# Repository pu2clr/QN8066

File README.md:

# [QN8066 FM DSP RX/TX  Arduino Library](https://pu2clr.github.io/QN8066/)

This library is intended to provide an easy-to-use interface for controlling the QN8066 FM transceiver and receiver. 

The primary goal of this Arduino library project for the QN8066 is to simplify the development of robust applications using this device. I hope that hobbyists, electronics technicians, radio amateurs, and others interested in this work will find success in their projects. All the C/C++ functions and methods are documented [here](https://pu2clr.github.io/QN8066/extras/apidoc/html/index.html).

This library can be freely distributed using the [MIT Free Software model](https://github.com/pu2clr/QN8066/blob/main/LICENSE). 
By using or installing this library, you are agreeing to the terms of the [MIT license](https://github.com/pu2clr/QN8066/blob/main/LICENSE). 

[Copyright (c) 2024 Ricardo Lima Caratti](https://github.com/pu2clr/QN8066/blob/main/LICENSE). 

Contact: __pu2clr@gmail.com__.

## About Me

I hold a Master's degree in Educational Technology from the Federal University of Ceará, where I delved into the ways technology can enhance learning experiences. My passion for computer science led me to specialize in it, focusing on Distributed Systems Development with an Object-Oriented approach, at the University of Brasília. My academic journey began with a Bachelor's degree in Information Systems from the União Pioneira de Integração Social (UPIS-Brasília). Outside the classroom, my main hobbies are electronics and Amateur Radio. 

## Notice to Users Regarding this Library

*This library is continuously evolving, with both corrective and feature updates. While the implemented functions have been tested, it is possible that in certain situations, the library may exhibit unexpected behavior. I encourage users to always utilize the latest release of this library. Should you encounter any issues, please feel free to contact me at pu2clr@gmail.com. I will do my best to address or clarify any problems as quickly as possible. Thank you.*

## Contents

1. [Legal Compliance Guidelines](./#legal-compliance-guidelines)
2. [QN8066 Arduino Library Features](./#qn8066-arduino-library-features)
2. [Technical Overview of the QN8066 RX/TX Device (IC)](./#technical-overview-of-the-qn8066-rxtx-device-ic)
3. [Why a QN8066 library for Arduino?](./#why-a-qn8066-library-for-arduino)
4. [Groups and Forums](./#groups-and-forums)
5. [QN8066 Functional Blocks](./#qn8066-functional-blocks)
6. [QN8066 PINOUT](./#qn8066-pinout)
7. [QN8066 Summary of User Control Registers](./#qn8066-summary-of-user-control-registers)
8. [QN8066 and Arduino based on ATmega328 or LGT8F328](./#qn8066-and-arduino-based-on-atmega328-or-lgt8f328)
9. [Homemade setup with the QN8066](./#homemade-setup-with-the-qn8066)
10. [DIY Kit 5W-7W FM Transceiver](./#diy-kit-5w-7w-fm-transceiver)
11. [Arduino Library Documentation](https://pu2clr.github.io/QN8066/extras/apidoc/html/index.html)
12. [**Arduino Sketch examples**](https://github.com/pu2clr/QN8066/tree/main/examples)
13. [Examples Index](./#examples-index)
14. [Boards where this library can be compiled](./#boards-where-this-library-can-be-compiled)
15. [Donate](./#donate)
16. [Most Frequent Problems](./#most-frequent-problems)
17. [References](./#references)

## Legal Compliance Guidelines

### Important Notice

It is important to emphasize that the project presented here is not intended to encourage anyone to violate their country’s regulations regarding radio frequency emissions. The goal of this project, centered around an Arduino library for controlling the QN8066, is to facilitate the development of diverse solutions involving this device.

Please, be aware that the use of FM transmitters is regulated by the laws and regulations of each country. **It is crucial to ensure that your use of any FM transmitter complies with the applicable legal requirements and does not violate any broadcasting regulations**.

### Legal Compliance Guidelines

1. **Frequency Range**: Ensure that the frequency range used by your FM transmitter is permitted in your country.
2. **Transmission Power**: Adhere to the maximum allowed transmission power to avoid interference with licensed broadcasters and other communication services.
3. **Licensing**: Check if a license is required to operate an FM transmitter in your region. Obtain the necessary permissions if required.
4. **Interference**: Avoid causing interference with other electronic devices and communication services. Ensure your setup follows the prescribed technical standards.
5. **Public Safety**: Be mindful of public safety and ensure your use of the FM transmitter does not pose any risks.

By following these guidelines, you can ensure that your use of the FM transmitter respects the laws and regulations of your country and does not result in any legal issues.

### Brazilian legislation notes

* Brazilian legislation allows some flexibility for the use of frequencies for research, experimentation, and educational purposes.
* FM transmitters with very low power (up to 0.5 mW) and short range can operate without a license. 
* Although amateur radio does not cover the commercial FM band, it is regulated by Anatel and permits transmission experimentation on other frequencies to promote technical learning.
* For educational or field transmissions, special authorization can be requested for specific events, such as science fairs or public demonstrations.
* Experimental transmissions may be allowed in controlled environments, such as laboratories, provided the signal does not exceed the physical boundaries of the location or interfere with other services.
* Microtransmitters or prototypes for short-range testing are tolerated as long as they operate within specific bands or with extremely low power.
* Wireless microphones based on FM transmitters are legal if they comply with designated sub-bands and power limits to prevent interference. 
* Community radio stations, limited to 25 watts and a 4 km radius, require licenses granted to non-profit organizations through the Ministry of Communications, with permits valid for 10 years and restrictions on commercial advertising.

# Groups and Forums

There is a Facebook group called [QN80XX FM Transmitters & Receivers Enthusiasts](https://www.facebook.com/groups/qn80xx)  where the purpose is exchanging experiences with projects based on Quintic QN80XX IC family. You will be welcome there.

## Donate 

If you find this project useful, consider making a donation so that the author of this library can purchase components and modules for improvements and testing of this library. [Click here to donate](https://www.paypal.com/donate/?business=LLV4PHKTXC4JW&no_recurring=0&item_name=Consider+making+a+donation.+So%2C+I+can+purchase+components+and+modules+for+improvements+and+testing+of+this+library.&currency_code=USD) or use the QR code below.

## Acknowledgements

* __Mr. Grazianny Carvalho Tavares__ - I would like to thank Mr. Grazianny Carvalho Tavares, PU7MGR, for introducing me to the QN8066 and encouraging me to develop this library. Mr. Grazianny also played a crucial role in helping me understand various concepts about FM modulation, audio quality criteria, as well as in testing the fundamental functions implemented in this library using equipment for precise value measurements.

* I would like to thank Mr. __Adam Fabio__ for his article published in the online magazine [Hackaday](https://hackaday.com) titled *[Be Your Own DJ With QN8066 And An Arduino Library](https://hackaday.com/2024/08/10/be-your-own-dj-with-qn8066-and-an-arduino-library/)*.

* I would like to thank Mr. __Gareth Halfacree__ for his article published in the online magazine  [hackster.io](https://www.hackster.io) titled *[Ricardo Lima Caratti's Handy Arduino Library Delivers Easy QN8066-Powered FM Radio Projects](https://www.hackster.io/news/ricardo-lima-caratti-s-handy-arduino-library-delivers-easy-qn8066-powered-fm-radio-projects-474213406313)*.

* Mr. Elionaldo Gomes da Silva, PY2EGS, to share his [board Layout project with Nano and LCD](./extras/schematics/NANO_LCD16x2_BOARD/)

## Why a QN8066 library for Arduino?

Technically, no Arduino application strictly requires a library. In some cases, avoiding libraries might even be the right decision. However, there are several compelling reasons to consider using them.

Libraries often simplify the design and maintenance of code, and they can make your projects more portable by implementing the necessary functionality across multiple hardware platforms.

For example, if you want to use an LCD or another display device in a project that monitors temperature and atmospheric pressure, there are many excellent libraries available for Arduino users. These libraries usually include most, if not all, of the features you might need. Re-inventing the wheel by not using a library generally doesn't make sense—unless you need a feature that no existing library supports. Using a library is often the smarter choice, particularly when it can simplify porting your code to different hardware.

Utilizing a library can reduce programming complexity and enhance the robustness of your application. It simplifies life not only for other developers but also for yourself. You don't need to be a software engineer to see the value in this. A library is similar to an integrated circuit (IC); while you could manually implement the functionality of many ICs in a circuit, doing so would significantly increase the cost, complexity, size, and potential for failure of your project. Often, it's better to abstract certain functions inside a ready-made IC. The user only needs to know how to interact with the chip, not how the chip itself is designed.

Finally, if you're already using libraries to handle the I2C bus (Wire.h), TFT or OLED displays, SPI devices, and Serial UART communication, it makes sense to use a library to manage the QN8066 device as well. The QN8066 Arduino Library can add convenience, development speed, and robustness to your project. Unlike closed-source solutions, this library is open-source, allowing you to learn from and modify the code as needed.

### Efficient Use of Libraries in Microcontroller Applications

Among the common myths about using this library alongside others is the assumption that it could significantly increase the final code size, making the application unfeasible for many microcontrollers. However, it is essential to highlight that, although the library contains extensive code, a large portion serves to provide directives to the C/C++ compiler and does not necessarily translate into executable code. Examples include type definitions (typedef), data structures (struct), and unions (union). Additionally, modern compilers and linkers offer powerful optimization features, notably [Link Time Optimization (LTO)](https://gcc.gnu.org/projects/lto/lto.pdf), which eliminates unused symbols and code, ensuring the final binary is lean and efficient. These optimizations, combined with dead code elimination and [inlining strategies](https://ethz.ch/content/dam/ethz/special-interest/infk/ast-dam/documents/Theodoridis-ASPLOS22-Inlining-Paper.pdf), reduce the overhead, making the use of complex libraries feasible even in resource-constrained environments.

In light of this, to make the most of your application, it is essential to have a deep understanding of the microcontroller architecture you are working with, as well as the tools you are using, such as the compiler and linker.

#### See also: 

 * [Inline Functions](https://isocpp.org/wiki/faq/inline-functions)
 * [Understanding and Exploiting Optimal Function Inlining](https://ethz.ch/content/dam/ethz/special-interest/infk/ast-dam/documents/Theodoridis-ASPLOS22-Inlining-Paper.pdf)
 * [Inline C++ code in embedded applications](https://blogs.sw.siemens.com/embedded-software/2020/07/20/inline-c-code-in-embedded-applications/)
 * [LLVM Link Time Optimization: Design and Implementation](https://llvm.org/docs/LinkTimeOptimization.html#llvm-link-time-optimization-design-and-implementation)
 * [What is Link Time Optimization (LTO)](https://developer.arm.com/documentation/101458/2404/Optimize/Link-Time-Optimization--LTO-/What-is-Link-Time-Optimization--LTO-)
 * [Link-Time Optimization in GCC: Requirements and High-Level Design](https://gcc.gnu.org/projects/lto/lto.pdf)
 * [How to use the typedef struct in C](https://www.educative.io/answers/how-to-use-the-typedef-struct-in-c)
 * [Structures, Typedef and Union in C Programming](https://binaryupdates.com/structures-typedef-union-in-c-programming/)
 * [Bit Fields in C](https://www.geeksforgeeks.org/bit-fields-c/)

## QN8066 Arduino Library Features

This library uses the I²C communication protocol and implements most of the functions offered by QN8066 IC from QUINTIC. This library also has primitive functions that make it easier for you to implement commands that may not have been implemented yet. As said before, this library is constantly improving. Check the API documentation before implementing a new function. It is likely that your function is already implemented. [See the API documentation for this library](https://pu2clr.github.io/QN8066/extras/apidoc/html/index.html). 

1. **Open Source**. It is free. You can use, copy, modify, merge, publish, distribute, sublicense, and/or sell copies of the Software. See [MIT License](https://github.com/pu2clr/QN8066/blob/main/LICENSE) to know more.   
2. Built based on QN8066 Datasheet
3. C++ Language and Object-oriented programming. You can easily extend the QN8066 class by adding more functionalities. 
4. **API Documentation**. All functions implemented in this library have documentation that can be checked in the source code or at this [link](https://pu2clr.github.io/QN8066/extras/apidoc/html/index.html)
4. Available on Arduino IDE (via Manage Libraries). Easy to install and use. 
5. **Cross-platform**. You can compile and run this library on most of boards supported by the Arduino IDE (Examples: ATtiny85, boards based on ATmega328 and ATmega-32u4, ATmega2560, ARM Cortex, STM32, Arduino DUE, ESP32 and more). 
6. Simplifies projects based on QN8066
7. [A lot of examples to guide the user](https://github.com/pu2clr/QN8066/tree/master/examples)
8. RDS support
9. **Clock reference selection** - The QN8066 has a pin (XCLC) that should be used to inject a signal that will be utilized by the IC as a reference clock. This signal can be 32.768 kHz or a multiple of this value. This library allows you to adapt your project to the active crystal you have available. See below for more details about it. 

## Technical Overview of the QN8066 RX/TX Device (IC)

### Introduction

The QN8066 is a highly integrated and versatile receiver/transmitter (RX/TX) device designed for use in FM radio applications. It offers a comprehensive solution for high-quality audio reception and transmission with minimal external components, making it suitable for a wide range of applications, including portable radios, automotive systems, and multimedia devices.

#### Key Features

- **Frequency Range**: The QN8066 operates over a wide frequency range, supporting FM band frequencies from 64 MHz to 108 MHz.
- **High Sensitivity**: The device is engineered to provide excellent sensitivity, allowing for clear reception of weak signals.
- **Integrated Analog and Digital Functions**: It includes both analog and digital components, ensuring compatibility with various audio formats and enhancing overall functionality.
- **Stereo Decoder**: The integrated stereo decoder ensures high-fidelity stereo audio output.
- **Low Power Consumption**: Designed with power efficiency in mind, the QN8066 is suitable for battery-powered devices, extending operational life.
- **Digital Signal Processing (DSP)**: Advanced DSP capabilities improve signal quality and reduce noise and interference.
- **Programmable Interface**: The QN8066 offers a flexible, programmable interface, enabling easy integration and customization for specific applications.

#### Technical Specifications

- **Operating Voltage**: The device operates at a typical voltage range of 2.7V to 3.6V.
- **Current Consumption**: It features low current consumption, typically around 20mA during active operation.
- **Output Power**: The output power is adjustable, catering to different transmission requirements.
- **Modulation Modes**: Supports various modulation modes including mono, stereo, and digital audio formats.
- **Interface**: I2C interface for easy communication with microcontrollers and other digital systems.

#### Applications

- **Portable Radios**: Due to its compact size and low power consumption, the QN8066 is ideal for portable radio applications.
- **Automotive Systems**: The high sensitivity and DSP capabilities make it suitable for in-car entertainment systems.
- **Multimedia Devices**: Compatible with a variety of audio sources, the QN8066 can be integrated into multimedia devices requiring FM reception and transmission capabilities.

## QN8066 Functional Blocks

1. **RF Front-End**: The RF front-end is designed to efficiently capture and process FM signals, ensuring minimal loss and high-quality signal reception.
2. **PLL Synthesizer**: The phase-locked loop (PLL) synthesizer ensures stable frequency generation and accurate tuning.
3. **Audio Processing**: Includes both analog and digital audio processing units to enhance sound quality and support various audio formats.
4. **Power Management**: Advanced power management features optimize power consumption, making the QN8066 ideal for portable applications.

### Attention

* __The Logic signals level of the QN8066 device (CEN, SCL, SDA, to GND) works from 1.6V to 3.6V (see Datasheet, ELECTRICAL SPECIFICATIONS, section Recommended Operating Conditions). If you are using a 5V Arduino board, that Arduino will send 5V signals to the QN8066 device through the digital pins and the I2C bus. That configuration can make the system unstable or damage the QN8066 device. To fix this, use a logic shifter chip that converts between 3.3V and 5V logic.__  

## QN8066 PINOUT 

### QN8066 Pin Descriptions

| SSOP16 PIN | NAME | DESCRIPTION |
| ------- | ---- | ----------- |
| 1       | SCL  | Clock for I2C serial bus |
| 2       | SDA  | Bi-directional data line for I2C serial bus |   
| 3       | VCC  | Voltage supply |
| 4       | ALO  | Analog audio output – left channel | 
| 5       | ARO  | Analog audio output – right channel |
| 6       | GND  | Ground | 
| 7       | RFI  | FM Receiver RF input |
| 8       | GND  | Ground |
| 9       | ARI  | Right channel audio input |
| 10      | ALI  | Left channel audio input | 
| 11      | GND  | Ground |
| 12      | RFO  | Transmitter RF output – connect to matched antenna |
| 13      | CEN  | Chip enable with internal pull up: Chip power down if less than 0 |4V and VIO is powered; power up if higher voltage or left floated |
| 14      | XCLK | External clock input | 
| 15      | GND Ground | 
| 16      | INT  | Interrupt output, active low, need pull-up externally | 

## QN8066 Summary of User Control Registers

| REGISTER  | NAME          | USER CONTROL FUNCTIONS |
| --------- | ------------- | ---------------------- | 
| 00h       | SYSTEM1       |  Sets device modes     |
| 01h       | SYSTEM2       |  Sets external clock type and CCA parameters |
| 02h       | CCA           | Sets CCA parameters |
| 03h       | SNR           | Estimate RF input CNR value |
| 04h       | RSSISIG       | In-band signal RSSI dBµ V value |
| 05h       | CID1          | Device ID numbers |
| 06h       | CID2          | Device ID numbers |
| 07h       | XTAL_DIV0     | Frequency select of reference clock source |
| 08h       | XTAL_DIV1     | Frequency select of reference clock source |
| 09h       | XTAL_DIV2     | Frequency select of reference clock source |
| 0Ah       | STATUS1       | System status |
| 0Bh       | RX_CH         | Lower 8 bit of 10-bit receiver channel index |
| 0Ch       | CH_START      | Lower 8 bits of 10-bit channel scan start channel index |
| 0Dh       | CH_STOP       | Lower 8 bits of 10-bit channel scan stop channel index |
| 0Eh       | CH_STEP       | Channel scan frequency step | Highest 2 bits of receiver channel indexes |
| 0Fh       | RX_RDSD0      | RDS data byte 0 |
| 10h       | RX_RDSD1      | RDS data byte 1 |
| 11h       | RX_RDSD2      | RDS data byte 2 |
| 12h       | RX_RDSD3      | RDS data byte 3 |
| 13h       | RX_RDSD4      | RDS data byte 4 |
| 14h       | RX_RDSD5      | RDS data byte 5 |
| 15h       | RX_RDSD6      | RDS data byte 6 |
| 16h       | RX_RDSD7      | RDS data byte 7 |
| 17h       | STATUS2       | Receiver RDS status indicators |
| 18h       | VOL_CTL       | Audio volume control |
| 19h       | INT_CTRL      | Receiver RDS control
| 1Ah       | STATUS3       | Receiver audio peak level and AGC status |
| 1Bh       | TXCH          | Lower 8 bit of 10-bit transmitter channel index |
| 1Ch       | TX_RDSD0      | Transmit RDS data byte0 |
| 1Dh       | TX_RDSD1      | Transmit RDS data byte1 |
| 1Eh       | TX_RDSD2      | Transmit RDS data byte2 |
| 1Fh       | TX_RDSD3      | Transmit RDS data byte3 |
| 20h       | TX_RDSD4      | Transmit RDS data byte4 | 
| 21h       | TX_RDSD5      | Transmit RDS data byte5 |
| 22h       | TX_RDSD6      | Transmit RDS data byte6 |
| 23h       | TX_RDSD7      | Transmit RDS data byte7 |
| 24h       | PAC           | PA output power target control | 
| 25h       | FDEV          | Specify total TX frequency deviation |
| 26h       | RDS           | Specify transmit RDS frequency deviation | 
| 27h       | GPLT          | Transmitter soft chip threshold, gain of TX pilot | 
| 28h       | REG_VGA       | TX AGC gain | 

## QN8066 and Arduino based on ATmega328 or LGT8F328

The following electrical circuit presents the basic interface configurations of the QN8066 device with an Arduino microcontroller based on the ATmega328 or equivalent, such as the LGT8F328.

**ATTENTION:** 
The QN8066 datasheet specifies a maximum digital interface voltage (SCL, SDA, INT, and CE) of 3.6V. Therefore, it's recommended to use Arduino boards that operate at 3.3V. In tests conducted by the author of this library, the Arduino Nano, which operates at 5V, worked without issues. However, it's important to note that this practice is not recommended and may pose a risk of damaging the QN8066. Alternatives include the LGT8F328 (a cheaper Nano-compatible version) and the Arduino Pro Mini (8MHz), both of which operate perfectly at 3.3V. Important: The author of this library is not responsible for any damages that may occur in your experiments based on the information shared in this documentation.

**The QN8066 depends on an active crystal (oscillator) for its operation. Although this library is configured for a 32.768 MHz crystal by default, it offers flexibility to accommodate other active crystal or signal generator frequencies. The following section outlines a few oscillator options suitable for the QN8066.**

## Homemade setup with the QN8066

The following figures illustrate a homemade setup with the QN8066. As you can see, only a few components are needed to build an FM transmitter with the QN8066. The goal here is provide a visual representation of a basic QN8066 circuit assembled on a breadboard. It's important to note that a 32.768 MHz active crystal is utilized in this particular setup.

The diagram below presents a fundamental setup of the QN8066 interfaced with an ATmega328 microcontroller.

The next prototype uses a 32.768 kHz active crystal, not a 32.768 MHz one. Even with a simpler setup, the circuit worked as expected. Both prototypes demonstrate how few components are needed for this system. 

Through some functions in the Arduino library, you can configure the active crystal you intend to use. Check the setup and begin functions for more details. 

The table below shows some tested sources (active crystal or signal generator) and divider values. 

|   Source (kHz)  | Divider       | 
| --------------  | ------------- |
|  32.768         |      1        | 
|  < 1,310.720    | did not work  |   
|  1,310.720      |    40         | 
|  1,638.400      |    50         | 
|  3,276.800      |   100         | 
|  13,107.200     |   400         | 
|  16,384.000     |   500         | 
|  32,768,000     |  1000         |  

**IMPORTANT:** As far as I understand, there is no possibility of using passive crystals. The QN8066 requires an active signal source provided by a generator.

#### Example 1

```cpp
/**

This sketch works on Arduino Pro Mini, Nano, UNO, or any other board based on the ATMega328. 
IMPORTANT: Refer to the documentation if you are using a 5V microcontroller instead of a 3.3V one.

This sketch illustrates the clock configuration used on the XCLK pin of the QN8066. 
Depending on the active crystal or signal generator you are using, it is important 
to set the correct frequency and signal waveform type for the QN8066 to function 
properly.

IMPORTANT: The QN8066 works with active crystals or signal generators. 
           Passive crystals will not work with the QN8066.

Author: Ricardo Lima Caratti (PU2CLR) - 2024
*/

#include <QN8066.h>
#define FREQUENCY 1069 // 106.9 MHz 
QN8066 tx;
char str[80];
void setup() {
  Serial.begin(9600);
  while (!Serial) ;
  delay(100); // Wait a bit while the system stabilizes.
  if (!tx.detectDevice()) {
    Serial.println("\nDevice QN8066 not detected");
    while (1);
  }
  // The call to the setup function below illustrates the use of a 32.768 kHz crystal. 
  // Since the reference clock for the QN8066 is exactly 32.768 kHz, you can provide the 
  // frequency value of the crystal you are using divided by 32.768. 
  // For example: if you are using a 32.768 kHz active crystal, then you should provide the 
  // divisor value of 1. If the signal generator (active crystal) produces a sine wave, 
  // enter the value 0, and if it is a digital signal, you should enter the value 1. See below.  
  tx.setup(1,      // Divider based on frequency select of reference clock source. The crystal used here is 32.768 kHz  
           false,  // Mono False => TX will start in stereo mode
           false,  // TX will start in RDS OFF
               1,  // PreEmphasis = 75
               1); // 1 if XCLK pin is receiving a digital clock. set it to 0 if you are using a sine-wave oscillator. 

  tx.setTX(FREQUENCY);    // Change the FREQUENCY constant if you want another value
  sprintf(str, "\n\nBroadcasting...");
  Serial.print(str);
}
void loop() {
    sprintf(str,"\nFSM: %d\nAudio Peak: %d mV", tx.getFsmStateCode(), tx.getAudioPeakValue());
    Serial.print(str);
    tx.resetAudioPeak();
    delay(15000);
}
```

#### Example 2

```cpp

#include <QN8066.h>
#define FREQUENCY 1069   // 106.9 MHz 
QN8066 tx;
char str[80];
void setup() {
  Serial.begin(9600);
  while (!Serial) ;
  delay(100); // Wait a bit while the system stabilizes.
  if (!tx.detectDevice()) {
    Serial.println("\nDevice QN8066 not detected");
    while (1);
  }
  tx.begin();
  // Assuming you are using a 32.768 kHz active crystal, a digital signal, and LO<RF, 
  // the image is on the lower side.
  tx.setXtal(1,1,0); 
  // tx.setXtal(100,1,0); // If you are using 3,276.8 kHz active crystal
  // tx.setXtal(1000,1,0); // If you are using 32,768 kHz active crystal
  delay(100);
  tx.setTX(FREQUENCY);    // Change the FREQUENCY constant if you want another value
  sprintf(str, "\n\nBroadcasting...");
  Serial.print(str);
}
void loop() {
    sprintf(str,"\nFSM: %d\nAudio Peak: %d mV", tx.getFsmStateCode(), tx.getAudioPeakValue());
    Serial.print(str);
    tx.resetAudioPeak();
    delay(15000);
}
```

## DIY Kit 5W-7W FM Transceiver

It is possible to find transceivers based on the QN8066 in kit form. With this library, you will also be able to control this kit, thereby expanding its original functionalities. Check AliExpress and other sources to find it. 

The images below show the DIY Kit 5W-7W FM Transceiver available on AliExpress.

### DIY Kit 5W-7W FM Transceiver assembled without the RF final amplifier 

### DIY Kit 5W-7W FM Transceiver assembled in a homemade case

### Using the QN8066 Arduino Library with DIY Kit 5W-7W FM Transceiver

The code below is a minimalist sketch example of using this library with the DIY Kit 5W-7W FM board. 

#### Arduino and the Kit 5W-7W FM connections

| Arduino Nano or Uno pin | Kit 5W-7W FM  |
| ----------------------- | ------------- | 
|          GND            |     GND       | 
|           D9            |     PWM (*1)  | 
|           A4            |     SDA (*2)  | 
|           A5            |     SCL (*2)  | 

##### (1) Communication Issue During PWM Signal Generation 

During experiments, commands sent to the QN8066 via I2C often had no effect, such as switching from "Stereo" to "Mono" or changing the transmission frequency. To resolve this, disable the PWM (0% duty cycle) before sending commands and re-enable it afterward.

```cpp
#include <QN8066.h>
QN8066 dv;
void setup() {
  Serial.begin(9600);
  while (!Serial); 
  pinMode(9, OUTPUT);  // Pin use to PWM power control
  dv.setup();
  Serial.print("\nStarting the system...");
  delay(1000);      
  dv.setTX(1067); // Set the transmitter to 106.7 MHz 
  dv.setTxStereo(true);
  // Now you can start PWM
  analogWrite(9, 50);  // It is about 1/5 of the max power (5~7W). It is between 1 and 1,4 W
  Serial.print("\nBroadcasting...");
  // Turning the Stereo OFF
  analogWrite(9, 0); // Disable PWM
  dv.setTxStereo(false);
  analogWrite(9, 50); // Enable PWM
}

void loop() {
}
```

##### (2) Compatibility Between the KIT and 5V Microcontroller Such as the Arduino Nano

The "DIY 5~7W FM Transmitter Kit" is designed for 3.3V controllers and has I2C pull-up resistors connected to its 3.3V power supply. However, the Arduino Nano operates at 5V, producing 5V signals on the I2C bus, which can cause communication instability. Additionally, the Nano cannot run stably on a 3.3V supply from the kit.

The simplest, but impractical, solution is to modify the Arduino Nano to run at 3.3V by changing its crystal to 8MHz and updating the bootloader. A better option is to use an **Arduino Pro Mini 3.3V** for direct compatibility.

In some examples using the Arduino Nano, a 3.3V to 5V voltage converter was added for power, along with two 150-ohm resistors in series with the I2C bus and two 10K resistors as pull-ups. While not ideal, this method works. A more appropriate solution would be to use a bidirectional I2C level shifter for compatibility.

The Arduino Nano is used in some examples in this library because it's popular among hobbyists, many of whom already have one or an Arduino Uno with the same architecture. Most other examples use 3.3V microcontrollers that do not require any modifications.

See also [DIY Kit 5W-7W FM example](https://github.com/pu2clr/QN8066/tree/main/examples/01_SERIAL_MONITOR/B_TX)

## DIY Kit 5W-7W FM connected with Arduino Pro Mini

The following figure shows the "DIY Kit 5W-7W FM TRANSMITTER" connected to the Arduino Pro Mini. The following link provides more operational details. [Click here to watch the video.](https://youtu.be/3V40yuwN-Vk?si=-umWUd4IRooRauze)

[Click here to see the source code and schematic](https://github.com/pu2clr/QN8066/tree/main/examples/03_LCD_16x2_AND_20x4)

### Some personal considerations about this KIT

Before presenting some observations that I consider important, it is worth highlighting that the following information may not reflect the reality in other environments or with other kits. The goal here is not to judge the quality of the kit or its architecture. However, these observations may explain some phenomena you might experience during the development of your project and help you mitigate these issues.

Based on several experiments I conducted with this kit, I observed instability in the communication between the microcontroller and the QN8066 via the I2C bus in the following situations:

1. **PWM Line Interference**: When the PWM line to control the transmitter's power is active, communication failures and even unavailability of the QN8066 to respond to new commands are common. One solution to this problem was to disable the PWM signal every time a command is sent to the system and re-enable the PWM signal afterward. It is important to note that this behavior hinders or limits, to some extent, a more dynamic use of RDS services.
   
2. **High Power Transmission**: When the transmitter is configured to transmit at higher power levels, approaching its upper limit of 7W, the communication also becomes unstable, and the QN8066 stops responding to the microcontroller, even though it continues to transmit.

3. **Avoid touching**: Touching certain points on the KIT board or the microcontroller with your hands can also cause system instability. 

4. **Wire-up organization**: Shortening and organizing the I2C bus lines that connect the KIT to the microcontroller significantly improves system stability. 

5. **Good grounding**: Through good grounding, it was possible to make the system more stable.

6. **System Stability of the KIT Powered via Microcontroller (Tests and Results)**: Without using the power module, that is, by only powering the QN8066 stage of the board through the interface connector with the microcontroller, the system remains stable. The example sketches provided in this library ran for hours without any instability. The sketch developed for the Arduino Pro Mini and LCD16x2 was subjected to a test lasting over 16 hours without any issues.

7. **Impact of RF Interference on I2C Communication in Power Control Systems**: There is another point to consider that might somewhat absolve the issue of power control via I2C. As the bandwidth increases, the transmitter's power also rises. It's possible that excessive RF signal in close proximity to the circuit is disrupting the I2C communication. When using a "dummy load," there is a noticeable reduction in I2C communication errors. This can be demonstrated by eliminating the I2C control and manually controlling it by applying a voltage of 3.3V or lower to the power control line. In my experiments, the I2C communication errors persisted, causing system instability.

8. **Enhancing System Stability Through Shielding and Isolation (Future Testing Considerations)**: Finally, I believe that good shielding of the KIT in a metal enclosure, as well as isolating the microcontroller from the transmitter (in a separate enclosure), could significantly improve the system. This is something to be tested in the future.

#### The following are some references to reports that may align with what was previously mentioned.

* [Dynamic_RDS - FM Transmitter Plugin for Falcon Player](https://github.com/ShadowLight8/Dynamic_RDS)

* [New 30W FM PLL Stereo Broadcast Transmitter Spectrum](https://youtu.be/l84aCG7SQ6M?si=fOy0QYjhkpQpiQg4)

It is important to highlight that this library was not developed exclusively to work with this kit. In fact, it was designed to work with any architecture involving the QN8066 via the I2C protocol. That said, it is crucial for the designer or experimenter to keep in mind the necessary precautions to provide a stable system. There are various literatures that can help follow the best design practices involving I2C communication.

### Considerations

In a new project involving the QN8066, I believe a more stable approach would be not to work with power levels above ½W on the same board. An additional amplification module could be added separately from the QN8066 circuit. The organization of the printed circuit board is also a determining factor in improving the stability of the system. Preferably, the communication circuit of the microcontroller with the QN8066 should be as far away as possible from the RF circuit. The appropriate values for the pull-up resistors for the I2C bus is a variable that deserves attention. These values may depend on the length of the bus and other I2C devices that may be connected to the circuit. In my experiments, I used 10K pull-up resistors. However, lower resistance values can be tested and may further improve the stability of the system. Consider shielding the Display and microcontroller circuit so that unwanted signals and interference do not propagate to the QN8066 circuit.

## Examples Index

This library includes a comprehensive collection of examples demonstrating various applications and configurations of the QN8066 FM transceiver. The examples are organized by hardware platform and functionality to help you quickly find the most suitable starting point for your project.

### Transmitter Examples

#### 1. [Basic TX Examples (Serial Monitor)](./examples/01_TX_SERIAL_MONITOR/)
Basic FM transmitter examples that demonstrate fundamental operations using the Serial Monitor for control and feedback.

1. [Device Detection](./examples/01_TX_SERIAL_MONITOR/A_DETECT_DEVICE/) - Simple device detection and basic setup
2. [Minimalist TX](./examples/01_TX_SERIAL_MONITOR/A_MINIMALIST_TX/) - Simplest possible FM transmitter implementation
3. [Basic TX with Full Setup](./examples/01_TX_SERIAL_MONITOR/A_TX/) - Complete basic transmitter with all features
4. [Advanced TX Control](./examples/01_TX_SERIAL_MONITOR/B_TX/) - Enhanced transmitter with advanced control options
5. [Crystal Clock Setup 1](./examples/01_TX_SERIAL_MONITOR/C_TX_CLOCK_CRYSTAL_SETUP1/) - Configuration for different crystal frequencies
6. [Crystal Clock Setup 2](./examples/01_TX_SERIAL_MONITOR/C_TX_CLOCK_CRYSTAL_SETUP2/) - Alternative crystal configuration methods

#### 2. [RDS Transmitter Examples](./examples/02_TX_RDS/)
Examples demonstrating Radio Data System (RDS) functionality for enhanced FM broadcasting.

1. [RDS Basic Implementation](./examples/02_TX_RDS/TX_RDS1/) - Basic RDS transmission with Program Service and Radio Text
2. [Advanced RDS Features](./examples/02_TX_RDS/TX_RDS2/) - Extended RDS functionality and dynamic content
3. [RDS with Real-Time Clock](./examples/02_TX_RDS/TX_RDS3_DATE_TIME_RTCDS1302/) - RDS with date/time using DS1302 RTC module

#### 3. [LCD Display Transmitter Examples](./examples/03_TX_LCD_16x2_AND_20x4/)
Complete FM transmitter projects with LCD display interfaces for user-friendly operation.

1. [Arduino Minimalist LCD](./examples/03_TX_LCD_16x2_AND_20x4/00_ARDUINO_MINIMALIST/) - Simple LCD-based transmitter
2. [Arduino Full LCD Interface](./examples/03_TX_LCD_16x2_AND_20x4/01_ARDUINO/) - Complete LCD transmitter with encoder control

#### 4. [Nokia Display Examples](./examples/04_NOKIA_DISPLAY/)
FM transmitter with Nokia 5110 display for compact, low-power applications.

1. [Basic Nokia Display](./examples/04_NOKIA_DISPLAY/BASIC_NOKIA_DISPLAY/) - FM transmitter with Nokia 5110 LCD

#### 5. [OLED I2C Display Examples](./examples/05_OLED_I2C/)
Modern OLED display implementations for high-contrast, easy-to-read interfaces.

1. [Basic OLED Transmitter](./examples/05_OLED_I2C/BASIC_OLED/) - FM transmitter with SSD1306 OLED display

### Microcontroller-Specific Examples

#### 6. [ATtiny8x Examples](./examples/06_TX_ATTINY8X/)
Compact implementations for resource-constrained ATtiny microcontrollers.

1. [ATtiny24 Transmitter](./examples/06_TX_ATTINY8X/TX_ATTINY24/) - Ultra-compact FM transmitter
2. [ATtiny44 with RDS and OLED](./examples/06_TX_ATTINY8X/TX_ATTINY44_RDS_OLED/) - Advanced features in minimal footprint
3. [ATtiny85 with RDS and OLED](./examples/06_TX_ATTINY8X/TX_ATTINY85_RDS_OLED/) - Maximum functionality in smallest package

#### 7. [ESP32 Examples](./examples/07_ESP32/)
Wi-Fi enabled transmitter applications with web interfaces and IoT capabilities.

1. [ESP32 with LCD and Encoder](./examples/07_ESP32/01_ESP32_LCD16x2_ENCODER/) - Traditional interface with Wi-Fi capability
2. [ESP32 Web Wi-Fi Control](./examples/07_ESP32/02_ESP32_WEB_WIFI_QN8066/) - Web-based transmitter control over Wi-Fi
3. [ESP32 Python Wi-Fi Interface](./examples/07_ESP32/03_ESP32_PYTHON_WIFI_QN8066/) - Python API for transmitter control
4. [ESP32 Access Point Portal](./examples/07_ESP32/04_ESP32_WEB_ACTIVE_PORTAL_QN8066/) - Standalone access point with web interface

#### 8. [STM32 Examples](./examples/08_STM32/)
High-performance implementations for STM32 ARM Cortex-M microcontrollers.

1. [STM32 with Encoder and LCD](./examples/08_STM32/STM32_ENCODER_LCD/) - Professional-grade transmitter control

#### 9. [ESP8266 Examples](./examples/09_ESP8266/)
Cost-effective Wi-Fi solutions for remote transmitter control.

1. [ESP8266 Access Point Web](./examples/09_ESP8266/ESP8266_ACCESS_POINT_WEB/) - Web interface via access point

#### 10. [Arduino Nano 33 IoT Examples](./examples/10_NANO_33_IOT/)
Modern Arduino with built-in Wi-Fi connectivity for IoT applications.

1. [Nano IoT with Encoder and LCD](./examples/10_NANO_33_IOT/NANO_IOT_ENCODER_LCD16x2/) - Traditional control with IoT capability
2. [Nano IoT Socket Interface](./examples/10_NANO_33_IOT/NANO_IOT_SOCKET/) - TCP socket communication with Python client
3. [Nano IoT Web Service](./examples/10_NANO_33_IOT/NANO_IOT_WEB_SERVICE/) - Web-based transmitter control

#### 11. [Raspberry Pi Pico Examples](./examples/11_RASPBERRY_PI_PICO/)
Examples for the popular RP2040-based development board.

1. [Basic Pico Transmitter](./examples/11_RASPBERRY_PI_PICO/BASIC_TX_PICO/) - Simple FM transmitter for Pico
2. [Pico with LCD and Encoder](./examples/11_RASPBERRY_PI_PICO/PICO_LCD16x2_ENCODER/) - Full-featured transmitter interface

### Receiver Examples

#### 12. [Basic Receiver Examples](./examples/50_RX_SERIAL_MONITOR/)
FM receiver implementations with serial monitor interface.

1. [Basic RX Implementation](./examples/50_RX_SERIAL_MONITOR/01_RX_A/) - Simple FM receiver with serial control

#### 13. [ESP32 Receiver with LCD](./examples/51_RX_LCD16X02_ESP32/)
ESP32-based FM receiver with LCD display and rotary encoder control.

#### 14. [ATmega328 Receiver with LCD](./examples/52_RX_LCD1602_ATMEGA328/)
Traditional Arduino Nano/Uno FM receiver with LCD interface.

### Utility and Development Tools

#### 15. [Development Tools](./examples/90_TOOLS/)
Useful utilities for development and testing.

1. [RTC DS1302 Tools](./examples/90_TOOLS/01_RTC_DS1302/) - Real-time clock configuration utilities
2. [STM32 RTC Tools](./examples/90_TOOLS/02_RTC_STM32/) - STM32 internal RTC configuration

#### 16. [Test Examples](./examples/98_TESTS/)
Various test implementations and experimental code.

1. [ATmega328 Tests](./examples/98_TESTS/02_ATMEGA328/) - Hardware compatibility tests
2. [3-Button LCD Interface](./examples/98_TESTS/ARDUINO_3_BUTTONS_LCD20x4_WITHOUT_RDS/) - Alternative control interface
3. [Encoder LCD without RDS](./examples/98_TESTS/ARDUINO_ENCODER_LCD12x2_WITHOUT_RDS/) - Simplified encoder interface
4. [Pro Mini with RTC](./examples/98_TESTS/PRO_MINI_3_BUTTONS_LCD16x2_RTC/) - Real-time clock integration

#### 17. [Under Construction](./examples/99_UNDER_CONSTRUCTION/)
Experimental and work-in-progress examples.

### Access Point Examples for Remote Control

The following examples demonstrate **Access Point functionality** for standalone operation without requiring external Wi-Fi networks:

- **[ESP8266 Access Point Web](./examples/09_ESP8266/ESP8266_ACCESS_POINT_WEB/)** - Creates "ESP8266_QN8066" network (password: 12345678), access via 10.0.0.2
- **[ESP32 Web Active Portal](./examples/07_ESP32/04_ESP32_WEB_ACTIVE_PORTAL_QN8066/)** - Creates "ESP32_QN8066" network (password: esp32qn8066), access via 10.0.0.1  
- **[Nano 33 IoT Web Service](./examples/10_NANO_33_IOT/NANO_IOT_WEB_SERVICE/)** - Creates "QN8066" network (password: qn8066123456), web interface at 10.0.0.1
- **[Nano 33 IoT Socket](./examples/10_NANO_33_IOT/NANO_IOT_SOCKET/)** - Creates "Nano33IoT_QN8066" network (password: 12345678), Python socket communication on port 8066

### Getting Started Recommendations

**For Beginners:**
- Start with [Minimalist TX](./examples/01_TX_SERIAL_MONITOR/A_MINIMALIST_TX/) for basic understanding
- Try [Basic OLED Transmitter](./examples/05_OLED_I2C/BASIC_OLED/) for a simple display interface

**For Arduino Users:**
- Use [Arduino Full LCD Interface](./examples/03_TX_LCD_16x2_AND_20x4/01_ARDUINO/) for complete functionality
- Try [Arduino Nano 33 IoT](./examples/10_NANO_33_IOT/) examples for Wi-Fi capability

**For IoT Applications:**
- Explore [ESP32 Examples](./examples/07_ESP32/) for advanced Wi-Fi features
- Use [Access Point examples](#access-point-examples-for-remote-control) for standalone operation

**For Low-Power Applications:**
- Check [ATtiny8x Examples](./examples/06_TX_ATTINY8X/) for minimal power consumption
- Consider [Arduino Pro Mini examples](./examples/03_TX_LCD_16x2_AND_20x4/) running at 3.3V

### Build and Compilation Tools

The examples folder also includes automated build tools:
- [compile.sh](./examples/compile.sh) - Linux/macOS compilation script for all examples
- [compile.bat](./examples/compile.bat) - Windows compilation script for all examples  
- [setup_libraries_boards.sh](./examples/setup_libraries_boards.sh) - Automated setup for Linux/macOS
- [setup_libraries_boards.bat](./examples/setup_libraries_boards.bat) - Automated setup for Windows
## Most Frequent Problems

1. Avoid using a computer connected to the mains during testing. The electrical grid can disturb the communication between the Arduino based board and the QN8066 device.
2. Check the I2C bus pull-up resistors.
3. Check the voltage on the digital pins of the QN8066.  It is not be greater than 3.6V.  
4. If you are using the Arduino Pro Mini 3.3V (8MHz), check the correct board on Arduino IDE Tools menu, Processor: __"Atmega328P (3.3V, 8MHz)"__. By default, the Arduino IDE uses the Pro Mini 5V processor version.
5. Do not try to power an ATmega328 Arduino Board designed to work with 5V and 16MHz with a 3.3V supply. That configuration will make your system unstable. See [ATmega328P Datasheet](http://ww1.microchip.com/downloads/en/DeviceDoc/Atmel-7810-Automotive-Microcontrollers-ATmega328P_Datasheet.pdf).
6. Do not try to power your Arduino based board designed to work with 3.3V with greater voltage. See the technical specifications of your Arduino Board and remember that the maximum voltage of the QN8066 digital interface is 3.6V.
7. During the implementation of your sketch, do not use high power (above 1/2 W) through an RF amplifier without proper shielding practices. The QN8066, particularly the I2C bus, is sensitive to spurious RF signals and may lose communication with the controller. Preferably, use a dummy load.
8. Avoid using long wiring for the I2C connection.
9. **Good grounding**: Through good grounding, it was possible to make the system more stable.

## References 

* [Be Your Own DJ With QN8066 And An Arduino Library](https://hackaday.com/2024/08/10/be-your-own-dj-with-qn8066-and-an-arduino-library/)
* [Best Practices for RDS Subcarrier Injection](https://www.radioworld.com/tech-and-gear/tech-tips/best-practices-for-rds-subcarrier-injection?fbclid=IwY2xjawEcUfVleHRuA2FlbQIxMAABHfP62aaiv6Ba38znsFZP59DjN_w-RoKoq6jDkiMpInU-6RAMLcs9__xXDg_aem_MDCR8KMYVsf8s-j5lSPxbA)
* [Bit Fields in C](https://www.geeksforgeeks.org/bit-fields-c/)
* [Broadcasting Audio Processing](http://help.stereotool.com/rds_encoder_texts.shtml?fbclid=IwY2xjawEdmv1leHRuA2FlbQIxMAABHelKGZt5WyDJ0g81BjrLtAnVXgE-TYcQrl0ErRSiTGA91CnuzZzSDbDlaQ_aem_3rO_AQELltf5jjZDPrsT3g)
* [Data Sheet - QUINTIC QN8066 Digital FM Transceiver for Portable Devices](https://vrtp.ru/index.php?act=Attach&type=post&id=913773)
* [Dynamic_RDS - FM Transmitter Plugin for Falcon Player](https://github.com/ShadowLight8/Dynamic_RDS)
* [How to use the typedef struct in C](https://www.educative.io/answers/how-to-use-the-typedef-struct-in-c)
* [Inline C++ code in embedded applications](https://blogs.sw.siemens.com/embedded-software/2020/07/20/inline-c-code-in-embedded-applications/)
* [Inline Functions](https://isocpp.org/wiki/faq/inline-functions)
* [Link-Time Optimization in GCC: Requirements and High-Level Design](https://gcc.gnu.org/projects/lto/lto.pdf)
* [LLVM Link Time Optimization: Design and Implementation](https://llvm.org/docs/LinkTimeOptimization.html#llvm-link-time-optimization-design-and-implementation)
* [NATIONAL RADIO SYSTEMS COMMITTEE NRSC-G300-A Radio Data System "RDS" Usage Guideline April 2014](https://www.nrscstandards.org/standards-and-guidelines/documents/archive/nrsc-g300-a.pdf)
* [Old Version of this library - Source 1](https://www.arduino.cc/reference/en/libraries/qn8066/)
* [Old Version of this library - Source 2](https://www.arduinolibraries.info/libraries/qn8066)
* [Radio Data System](https://en.wikipedia.org/wiki/Radio_Data_System)
* [RDS Encoder Version 1.5 Implementation Manual](https://www.pira.cz/rds/readbest.pdf)
* [Ricardo Lima Caratti's Handy Arduino Library Delivers Easy QN8066-Powered FM Radio Projects](https://www.hackster.io/news/ricardo-lima-caratti-s-handy-arduino-library-delivers-easy-qn8066-powered-fm-radio-projects-474213406313)
* [Structures, Typedef and Union in C Programming](https://binaryupdates.com/structures-typedef-union-in-c-programming/)
* [UNIVERSITY COLLEGE LONDON Department of Electronics and Electrical Engineering](https://haddadi.github.io/papers/RDSencoderHaddadi.pdf)
* [Understanding and Exploiting Optimal Function Inlining](https://ethz.ch/content/dam/ethz/special-interest/infk/ast-dam/documents/Theodoridis-ASPLOS22-Inlining-Paper.pdf)
* [What is Link Time Optimization (LTO)](https://developer.arm.com/documentation/101458/2404/Optimize/Link-Time-Optimization--LTO-/What-is-Link-Time-Optimization--LTO-)
* [FM Transmitter Remotely Controlled Via ESP32](https://blog.pishop.co.za/fm-transmitter-remotely-controlled-via-esp32/)
* [FM Transmitter Remotely Controlled Via ESP32](https://hackaday.com/2024/10/18/fm-transmitter-remotely-controlled-via-esp32/)

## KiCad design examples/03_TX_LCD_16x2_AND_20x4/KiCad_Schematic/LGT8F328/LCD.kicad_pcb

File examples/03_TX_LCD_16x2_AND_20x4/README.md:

# QN8066 Arduino Library and LCD 16x02 examples

The sketches provided in this repository have been thoroughly tested and verified to work seamlessly on Arduino Uno, Nano, Pro Mini, and LGT8F328 boards. However, to ensure optimal performance and avoid potential issues, please carefully review the best practices outlined in the documentation for the QN8066 module, your specific controller board, and this repository. 

**Please note that the ESP32 version, found in this folder, has some variations in pin mappings and EEPROM handling compared to the Arduino and LGT8F328 versions. For specific details on these differences, consult the documentation within the sketch.**

The sketch found in the **00_ARDUINO_MINIMALIST** folder is a basic version designed to guide users in creating their own projects with LCD16x2, LCD20x4, or other LCD displays. As a result, no user controls are implemented in this sketch.

## Arduino Nano or LGT8F328P and "KIT DIY 5~7W FM TRANSMITTER" schematic

The following schematic illustrates the connections between the Arduino Nano, the "KIT DIY 5~7W FM TRANSMITTER," and either the LCD 16x2 or the LCD 20x4. It is important to note that both the LCD 16x2 and the LCD 20x4 have the same pin configuration. This means that there are no electrical changes when using one or the other.

### Regular LCD16x02 (5V) 

## Wire up on Arduino UNO, Nano or Pro mini

### LCD 16x2 or 20x4  

  | LCD                       | Device Pin / Label        |  Arduino Pin  |
  | ------------------------- | ------------------------- | ------------  |
  | LCD 16x2 or 20x4          | D4                        |     D7        |
  |                           | D5                        |     D6        |
  |                           | D6                        |     D5        |
  |                           | D7                        |     D4        |
  |                           | RS                        |     D12       |
  |                           | E/ENA                     |     D13       |
  |                           | RW & VSS & K (16)         |    GND        |
  |                           | A (15) & VDD              |    +Vcc       |

### DIY KIT 5˜7W FM TRANSMITTER

  | DIY KIT 5˜7W FM TRANSM.   | Device Pin / Label        |  Arduino Pin  |
  | --------------------------| ------------------------- | --------------|
  | QN8066 BOARD              | SDA  (see *2)             |     A4        |
  |                           | SCLK (see *2)             |     A5        |
  |                           | PWM  (see *1)             |     D9        |

### Buttons 
  
  | Buttons                   | Device Pin / Label        |  Arduino Pin  |
  | ------------------------- | ------------------------- | --------------|
  |                           | Menu                      |      8        |
  |                           | Left (Down / -)           |     10        |
  |                           | Right (Up / + )           |     11        |

### IMPORTANT

#### (1) Communication Problem Between the KIT and the Microcontroller with PWM

**During various experiments, it was observed that several commands sent to the QN8066 (via I2C) had no effect. For instance, attempts to switch from "Stereo" to "Mono" mode, change the transmission frequency, among other commands, did not alter the transmitter's status. To work around this issue, the PWM must be disabled first, meaning it should not generate a pulse (0% duty cycle). After the command is sent, the PWM signal can be re-enabled. Doing that the system works well.**

#### (2) Compatibility Between the KIT and 5V Microcontroller Such as the Arduino Nano

**There are some important considerations when using a microcontroller like the Arduino Nano with the "DIY 5~7W FM Transmitter Kit". This kit is designed to work with a 3.3V controller, meaning the I2C bus is configured with pull-up resistors connected to the board's power supply. However, the Arduino Nano operates at 5V, producing a 5V signal on the I2C bus, which can cause instability in I2C communication. Additionally, the Arduino Nano will not operate stably when powered by a 3.3V supply (provided by the kit)**.

**The most straightforward and suitable solution, though not very practical, would be to modify the Arduino Nano to operate at 3.3V (by changing the crystal to 8MHz, among other modifications, including changing the bootloader). The most viable solution would be to use an "Arduino Pro Mini 3.3V". This way, no changes or adaptations would be necessary to connect the kit to the microcontroller**.

**For the Arduino Nano, the adaptation used in this example involves using a 3.3V to 5V voltage converter to power the Arduino and placing two 150-ohm resistors in series with the I2C bus and two pull-up 10K resistors connected to the I2C wires.  Although this is not best practice, it works to some extent. If you insist in using a Arduino Nano, a more appropriate solution would be to use a bidirectional I2C level shifter to make the I2C communication compatible with both the Arduino Nano and the kit**.

**Finally, the Arduino Nano was used in this example because it is widely used by most hobbyists. It's likely that many already have one at home, or even an Arduino Uno, which shares the same architecture**. 

**The LGT8F328P is a microcontroller that is designed to be compatible with the popular ATmega328P,  which is widely used in Arduino boards like the Arduino Uno. The LGT8F328P is manufactured by LogicGreen and is often considered a more cost-effective or feature-rich alternative to the ATmega328P. One advantage of using the LGT8F328 board over the Nano is that, in addition to having the same pin configuration as the Nano V3, it operates at 3.3V, allowing for direct integration with the QN8066 if additional resources are required.** 

#### An alternative of connecting Arduino Nano and the KIT 

An alternative version that worked in my experiments, using a makeshift adaptation, does not follow the best practices for compatibility.

## Arduino Pro mini schematic 

An alternative version that worked in my experiments uses a makeshift adaptation and does not follow best practices for compatibility.

### LCD16x02 3.3V Version

### LCD16x02 5V modified to operate with 3.3V

The IC labeled "7660 AIBAZ DNY17P" is commonly known as the ICL7660. It is a DC-DC voltage converter that functions as a voltage inverter, converting a positive voltage to a negative voltage. This chip is widely used in applications where a negative voltage is needed from a positive power supply. In this case, you use it as a Voltage Doubler. 

  3.3V ---+---[7660]---+----> +6.6V (VOUT)

          |            |

         [C1]         [C2]

          |            |

         GND          GND

C1 and C2 are 10µF capacitors.

## STANDALONE ATMEGA328 WITH MENU CONTROLLED BY ENCODER

The STANDALONE ATMEGA328 version refers to using the ATmega328 microcontroller without the configurations found on Arduino boards. This setup requires a different programming interface (ISP) as well as specific settings for compilation. The crystal shown in the following circuit is optional. The ATmega328 can be configured with its internal 8MHz oscillator without any detriment to the application.

### Schematic

### Standalone ATmega328 Prptotype

Both the schematic and the sketch apply to the Arduino UNO, Nano, Pro Mini, or any other board based on the ATmega328. The operating voltage of each architecture should be considered according to the recommendations provided earlier.

### Wire up using the standalone ATmega328

The wiring for the standalone ATmega328 is the same as with the Nano, Uno, or Pro Mini versions. I only changed the menu button to digital pin D14/A0 to make it easier. But you can keep it on pin 8 if you want, just be careful with the physical connections.
It is worth noting that the Up/Right and Down/Left buttons have been replaced by the encoder, which uses pins 2 and 3 of the Arduino/ATmega328. This change is beneficial because these pins allow for interrupt configuration, making the interface more responsive.

| Device name               | Device Pin / Description  |  Arduino Pin  |
| --------------------------| --------------------      | ------------  |
|    LCD 16x2 or 20x4       |                           |               |
|                           | D4                        |     D7        |
|                           | D5                        |     D6        |
|                           | D6                        |     D5        |
|                           | D7                        |     D4        |
|                           | RS                        |     D12       |
|                           | E/ENA                     |     D13       |
|                           | RW & VSS & K (16)         |    GND        |
|                           | A (15) & VDD              |    +Vcc       |
| --------------------------| ------------------------- | --------------|
| QN8066                    |                           |               |
| DIY KIT 5˜7W              | ------------------------- | --------------|
|                           | SDA                       |     A4        |
|                           | SCLK                      |     A5        |
|                           | PWM                       |     D9        |
| --------------------------| --------------------------| --------------|
| Button                    |                           |               |
|                           | Menu                      |     D8        |
| Encoder                   |                           |               | 
|                           | Left                      |     D2        |
|                           | Right                     |     D3        |
| --------------------------| --------------------------|---------------|

### Arduino Nano or LGT8F328 with encoder and DS1302 RTC schematic

The following schematic presents a version of the controller with the LGT8F328 microcontroller integrated with an LCD, a Rotary Encoder, and a real-time clock based on the DS1302.

## Videos related to this example

* [QN8066 Arduino Library by PU2CLR - Part 2](https://youtu.be/3V40yuwN-Vk?si=ZDTcvcty_OK6Nm9N)
* [QN8066 Arduino Library by PU2CLR - Part 1](https://youtu.be/C69MqLq1cw8?si=xd4P6nIfzfCbaN0_)
* [QN8066 RX/TX FM DSP Arduino Library](https://youtu.be/cNQA_2QtBZk?si=Li1ocRp1A5LYIRh8)

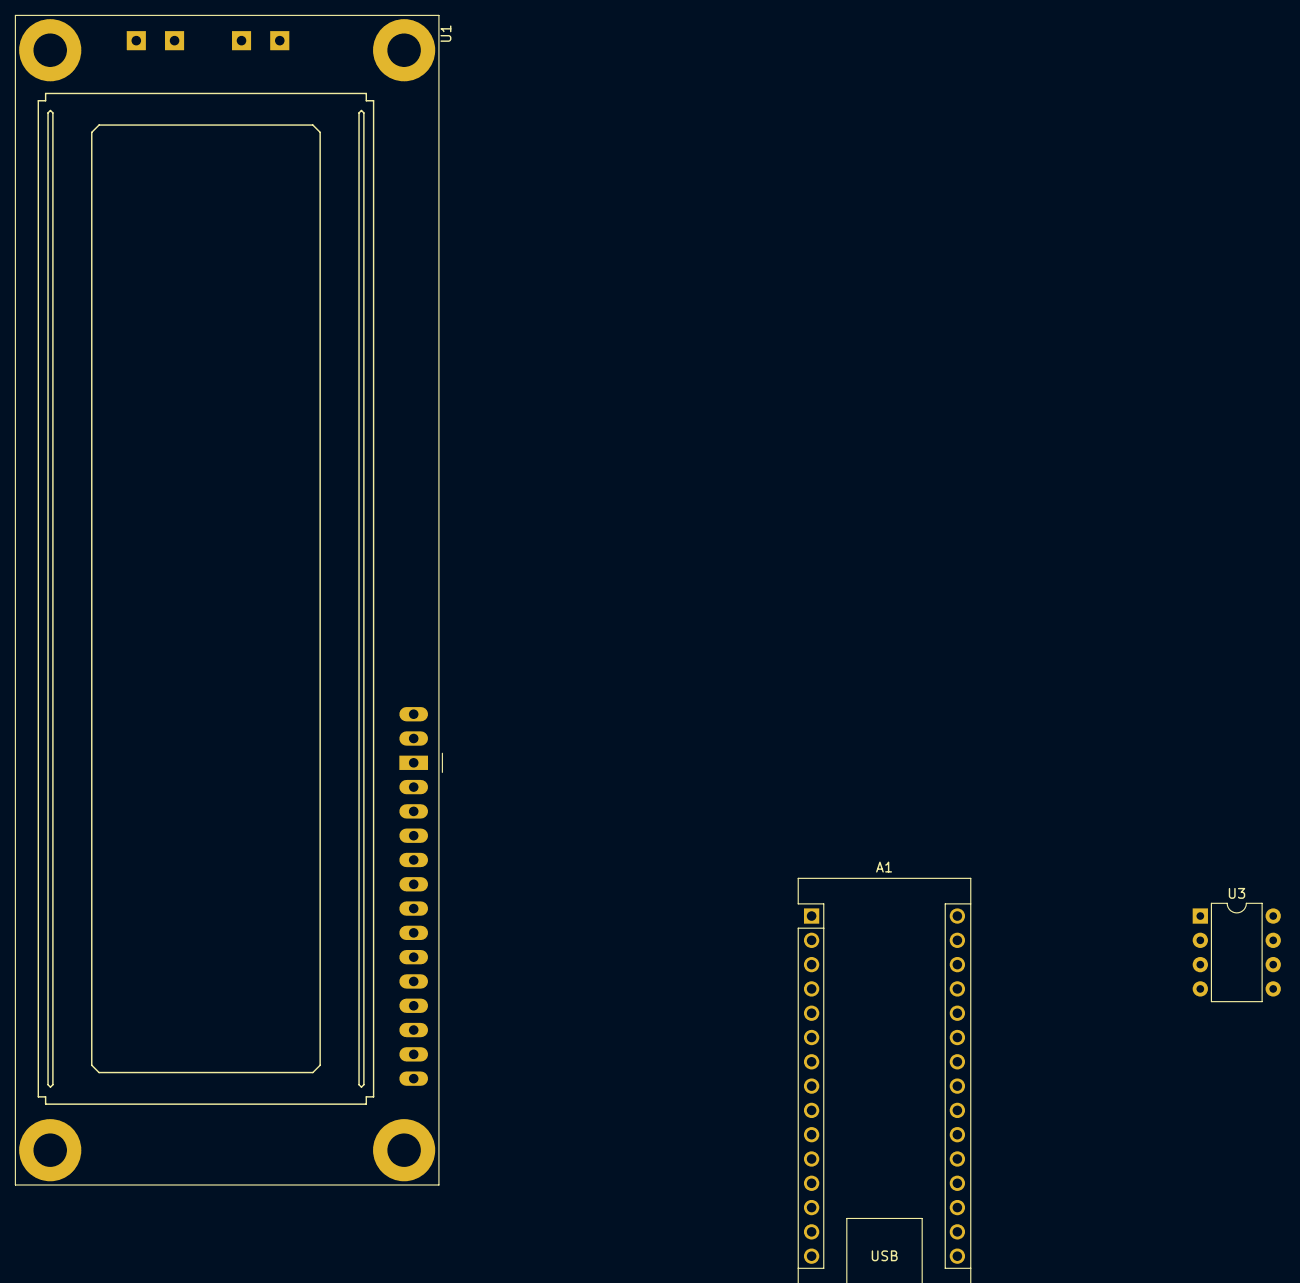
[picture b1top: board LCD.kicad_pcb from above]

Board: 2 copper layers, 3 parts (0 on the bottom side), 11 nets, no tracks yet.

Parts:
A1: LGT8F328; Arduino_Nano
U1: LCD 16x02 or 20x04; LCD-016N002L
U3: DS1302+; DIP-8_W7.62mm

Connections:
+3V3: A1.30 (VIN), U1.2 (VDD), U1.A2, U3.1 (VCC2)
GND: A1.4 (GND), A1.29 (GND), U1.1 (VSS), U1.5 (R/~W), U1.K2, U3.4 (GND)
unnamed: A1.19 (A0), U3.7 (SCLK)
unnamed: A1.20 (A1), U3.6 (I/O)
unnamed: A1.21 (A2), U3.5 (CE)
unnamed: A1.7 (D4), U1.14 (DB7)
unnamed: A1.8 (D5), U1.13 (DB6)
unnamed: A1.9 (D6), U1.12 (DB5)
unnamed: A1.10 (D7), U1.11 (DB4)
unnamed: A1.15 (D12), U1.4 (RS)
unnamed: A1.16 (D13), U1.6 (E)

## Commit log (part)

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2024-08-12 Test
2024-09-20 Docx
2024-09-28 Documentation
2024-10-10 Docs
2025-12-09 Doc Proteus
